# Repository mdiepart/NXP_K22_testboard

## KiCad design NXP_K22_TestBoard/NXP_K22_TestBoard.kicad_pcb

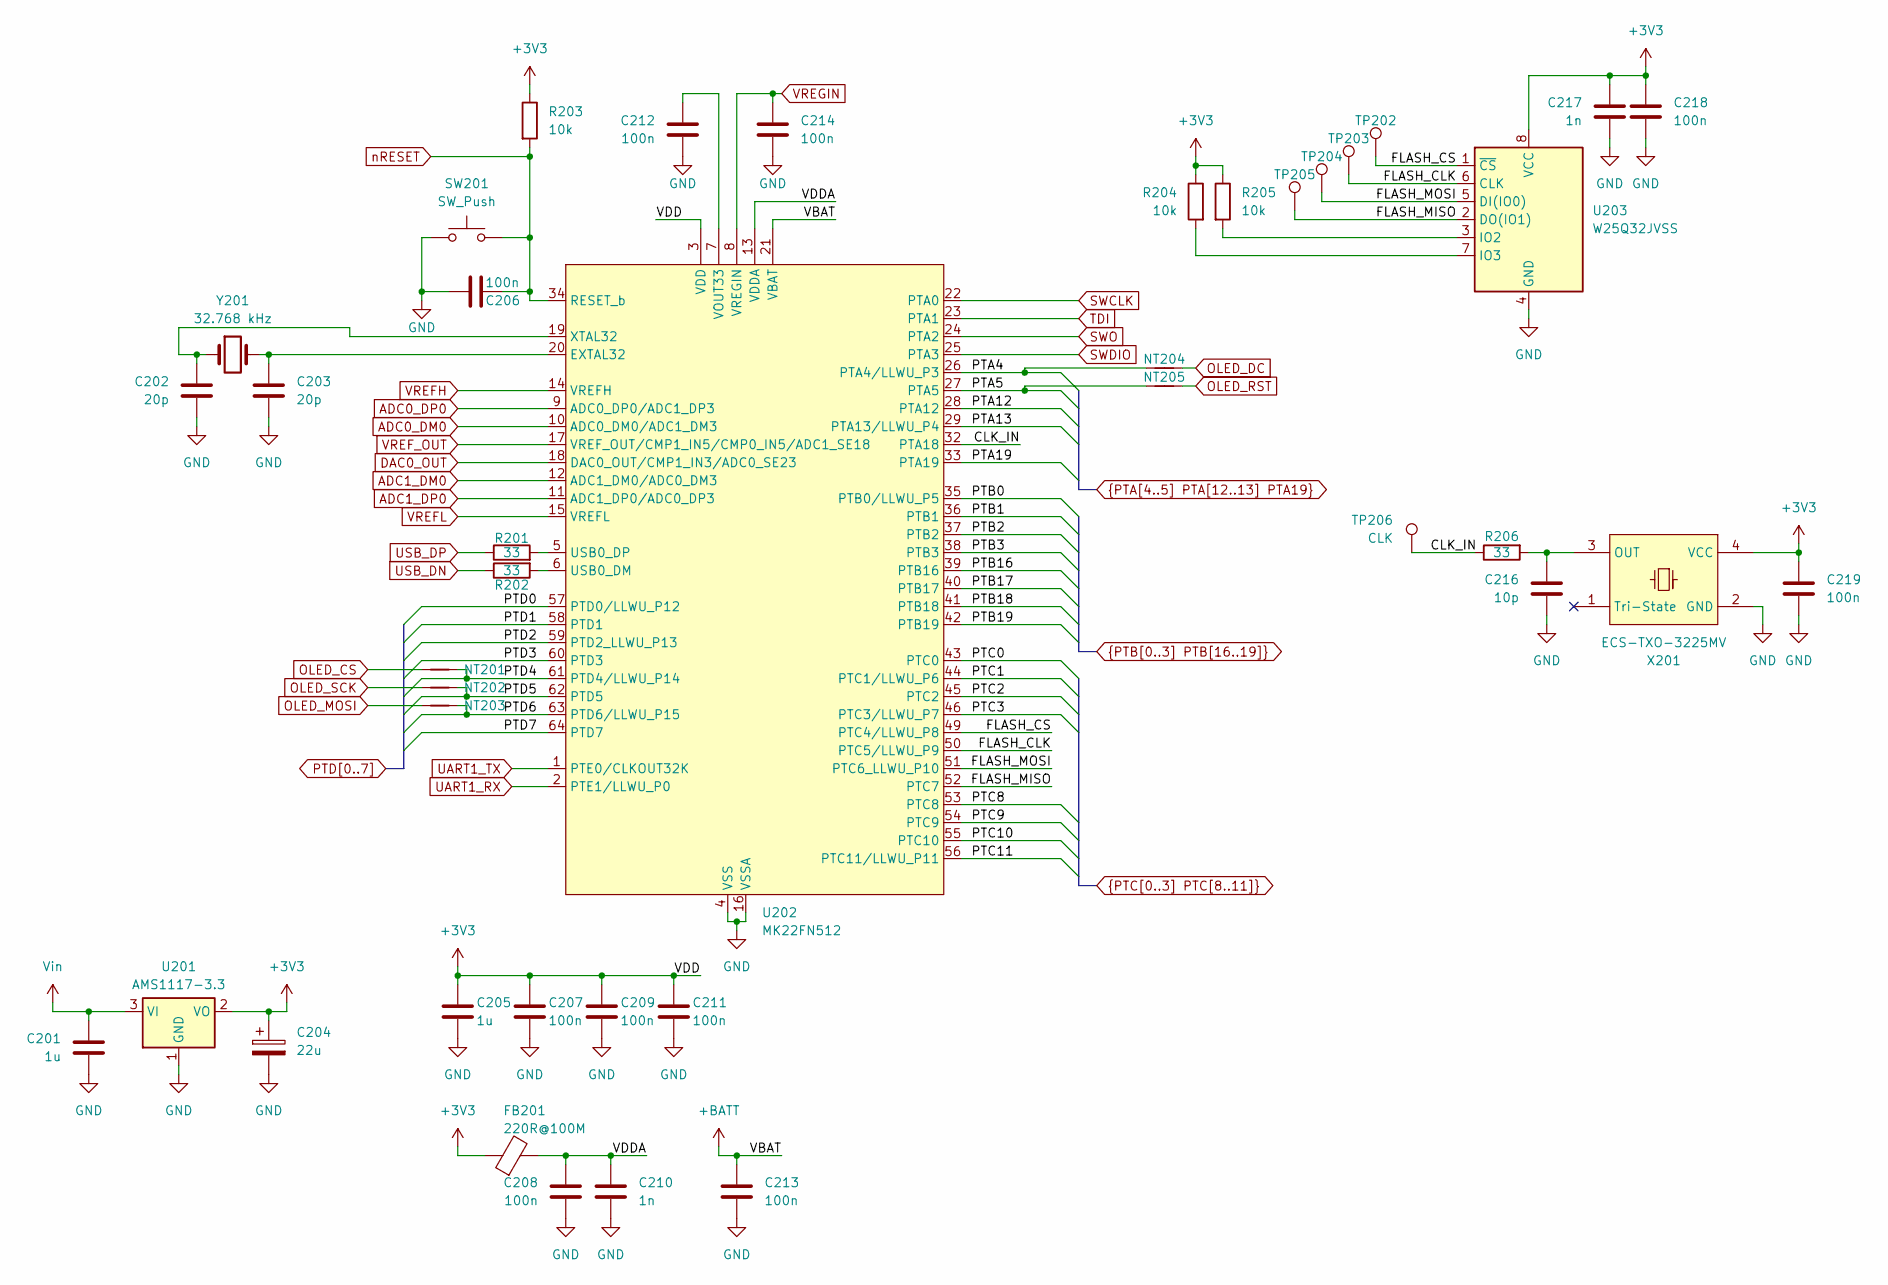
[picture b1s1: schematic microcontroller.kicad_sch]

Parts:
C201, C205: 1u; C_0603_1608Metric; MPN Generic C/1uF/X7R/50V/0603
C202, C203: 20p; C_0603_1608Metric; MPN Generic C/12pF/C0G/50V/0603
C204: 22u; CP_EIA-7343-31_Kemet-D; MPN T495D226K035ATE125; LCSC Part # C122325
C206, C207, C208, C209, C211, C212, C213, C214, C218, C219: 100n; C_0603_1608Metric; MPN Generic C/100nF/X7R/16V/0603
C210, C217: 1n; C_0603_1608Metric; MPN Generic C/1nF/X7R/16V/0603
C216: 10p; C_0603_1608Metric; MPN Generic C/10pF/C0G/50V/0603
FB201: 220R@100M; L_0603_1608Metric; MPN MPZ1608Y221BTA00; LCSC Part # C275489
NT201, NT202, NT203, NT204, NT205: NetTie_2; NetTie-2_SMD_Pad0.2mm
R201, R202, R206: 33; R_0603_1608Metric; MPN Generic R/33R/0603
R203, R204, R205: 10k; R_0603_1608Metric; MPN Generic R/10k/0603
SW201: SW_Push; SW_SPST_PTS645; MPN PTS645SH50SMTR92LFS; LCSC Part # C221869
TP202, TP203, TP204, TP205: TestPoint; TestPoint_Pad_D1.5mm
TP206: CLK; TestPoint_Pad_D2.0mm
U201: AMS1117-3.3; SOT-223-3_TabPin2; MPN AMS1117-3.3; LCSC Part # C6186
U202: MK22FN512; LQFP-64_10x10mm_P0.5mm; MPN MK22FN512VLH12
U203: W25Q32JVSS; SOIC-8_5.23x5.23mm_P1.27mm; MPN W25Q32JVSSIQ; LCSC Part # C179173
X201: ECS-TXO-3225MV; ECS-TXO_3.2x2.5mm; MPN ECS-TXO-3225MV-122.8-TR; LCSC Part # C5355149
Y201: 32.768 kHz; Crystal_SMD_3215-2Pin_3.2x1.5mm; MPN Q13FC1350000400; LCSC Part # C32346

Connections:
+3V3: C204.1, C205.1, C207.1, C209.1, C211.1, C217.1, C218.1, C219.1, FB201.1, R203.1, R204.1, R205.1, U201.2 (VO), U202.3 (VDD), U202.30 (VDD), U202.48 (VDD), U203.8 (VCC), X201.4 (VCC); also elsewhere on the board
+BATT: C213.1, U202.21 (VBAT); also elsewhere on the board
/Microcontroller/CLK_IN: R206.1, TP206.1, U202.32 (PTA18)
/Microcontroller/FLASH_CLK: TP203.1, U202.50 (PTC5/LLWU_P9), U203.6 (CLK)
/Microcontroller/FLASH_CS: TP202.1, U202.49 (PTC4/LLWU_P8), U203.1 (~CS)
/Microcontroller/FLASH_MISO: TP205.1, U202.52 (PTC7), U203.2 (DO(IO1))
/Microcontroller/FLASH_MOSI: TP204.1, U202.51 (PTC6_LLWU_P10), U203.5 (DI(IO0))
/Microcontroller/VDDA: C208.1, C210.1, FB201.2, U202.13 (VDDA)
ADC0_DM0: U202.10 (ADC0_DM0/ADC1_DM3); also elsewhere on the board
ADC0_DP0: U202.9 (ADC0_DP0/ADC1_DP3); also elsewhere on the board
ADC1_DM0: U202.12 (ADC1_DM0/ADC0_DM3); also elsewhere on the board
ADC1_DP0: U202.11 (ADC1_DP0/ADC0_DP3); also elsewhere on the board
DAC0_OUT: U202.18 (DAC0_OUT/CMP1_IN3/ADC0_SE23); also elsewhere on the board
GND: C201.2, C202.2, C203.2, C204.2, C205.2, C206.2, C207.2, C208.2, C209.2, C210.2, C211.2, C212.2, C213.2, C214.2, C216.2, C217.2, C218.2, C219.2, SW201.1, U201.1 (GND), U202.4 (VSS), U202.16 (VSSA), U202.31 (VSS), U202.47 (VSS), U203.4 (GND), X201.2 (GND); also elsewhere on the board
unnamed: C203.1, U202.20 (EXTAL32), Y201.2
unnamed: R202.2, U202.6 (USB0_DM)
unnamed: R201.2, U202.5 (USB0_DP)
unnamed: C212.1, U202.7 (VOUT33)
unnamed: C202.1, U202.19 (XTAL32), Y201.1
unnamed: R205.2, U203.3 (IO2)
unnamed: R204.2, U203.7 (IO3)
unnamed: C216.1, R206.2, X201.3 (OUT)
OLED_CS: NT201.1; also elsewhere on the board
OLED_DC: NT204.2; also elsewhere on the board
OLED_MOSI: NT203.1; also elsewhere on the board
OLED_RST: NT205.2; also elsewhere on the board
OLED_SCK: NT202.1; also elsewhere on the board
PTA4: NT204.1, U202.26 (PTA4/LLWU_P3); also elsewhere on the board
PTA5: NT205.1, U202.27 (PTA5); also elsewhere on the board
PTA12: U202.28 (PTA12); also elsewhere on the board
PTA13: U202.29 (PTA13/LLWU_P4); also elsewhere on the board
PTA19: U202.33 (PTA19); also elsewhere on the board
PTB0: U202.35 (PTB0/LLWU_P5); also elsewhere on the board
PTB1: U202.36 (PTB1); also elsewhere on the board
PTB2: U202.37 (PTB2); also elsewhere on the board
PTB3: U202.38 (PTB3); also elsewhere on the board
PTB16: U202.39 (PTB16); also elsewhere on the board
PTB17: U202.40 (PTB17); also elsewhere on the board
PTB18: U202.41 (PTB18); also elsewhere on the board
PTB19: U202.42 (PTB19); also elsewhere on the board
PTC0: U202.43 (PTC0); also elsewhere on the board
PTC1: U202.44 (PTC1/LLWU_P6); also elsewhere on the board
PTC2: U202.45 (PTC2); also elsewhere on the board
PTC3: U202.46 (PTC3/LLWU_P7); also elsewhere on the board
PTC8: U202.53 (PTC8); also elsewhere on the board
PTC9: U202.54 (PTC9); also elsewhere on the board
PTC10: U202.55 (PTC10); also elsewhere on the board
PTC11: U202.56 (PTC11/LLWU_P11); also elsewhere on the board
PTD0: U202.57 (PTD0/LLWU_P12); also elsewhere on the board
PTD1: U202.58 (PTD1); also elsewhere on the board
PTD2: U202.59 (PTD2_LLWU_P13); also elsewhere on the board
PTD3: U202.60 (PTD3); also elsewhere on the board
PTD4: NT201.2, U202.61 (PTD4/LLWU_P14); also elsewhere on the board
PTD5: NT202.2, U202.62 (PTD5); also elsewhere on the board
PTD6: NT203.2, U202.63 (PTD6/LLWU_P15); also elsewhere on the board
PTD7: U202.64 (PTD7); also elsewhere on the board
SWCLK: U202.22 (PTA0); also elsewhere on the board
SWDIO: U202.25 (PTA3); also elsewhere on the board
SWO: U202.24 (PTA2); also elsewhere on the board
TDI: U202.23 (PTA1); also elsewhere on the board
UART1_RX: U202.2 (PTE1/LLWU_P0); also elsewhere on the board
UART1_TX: U202.1 (PTE0/CLKOUT32K); also elsewhere on the board
USB_DN: R202.1; also elsewhere on the board
USB_DP: R201.1; also elsewhere on the board
VREFH: U202.14 (VREFH); also elsewhere on the board
VREFL: U202.15 (VREFL); also elsewhere on the board
VREF_OUT: U202.17 (VREF_OUT/CMP1_IN5/CMP0_IN5/ADC1_SE18); also elsewhere on the board
VREGIN: C214.1, U202.8 (VREGIN); also elsewhere on the board
Vin: C201.1, U201.3 (VI); also elsewhere on the board
nRESET: C206.1, R203.2, SW201.2, U202.34 (RESET_b); also elsewhere on the board

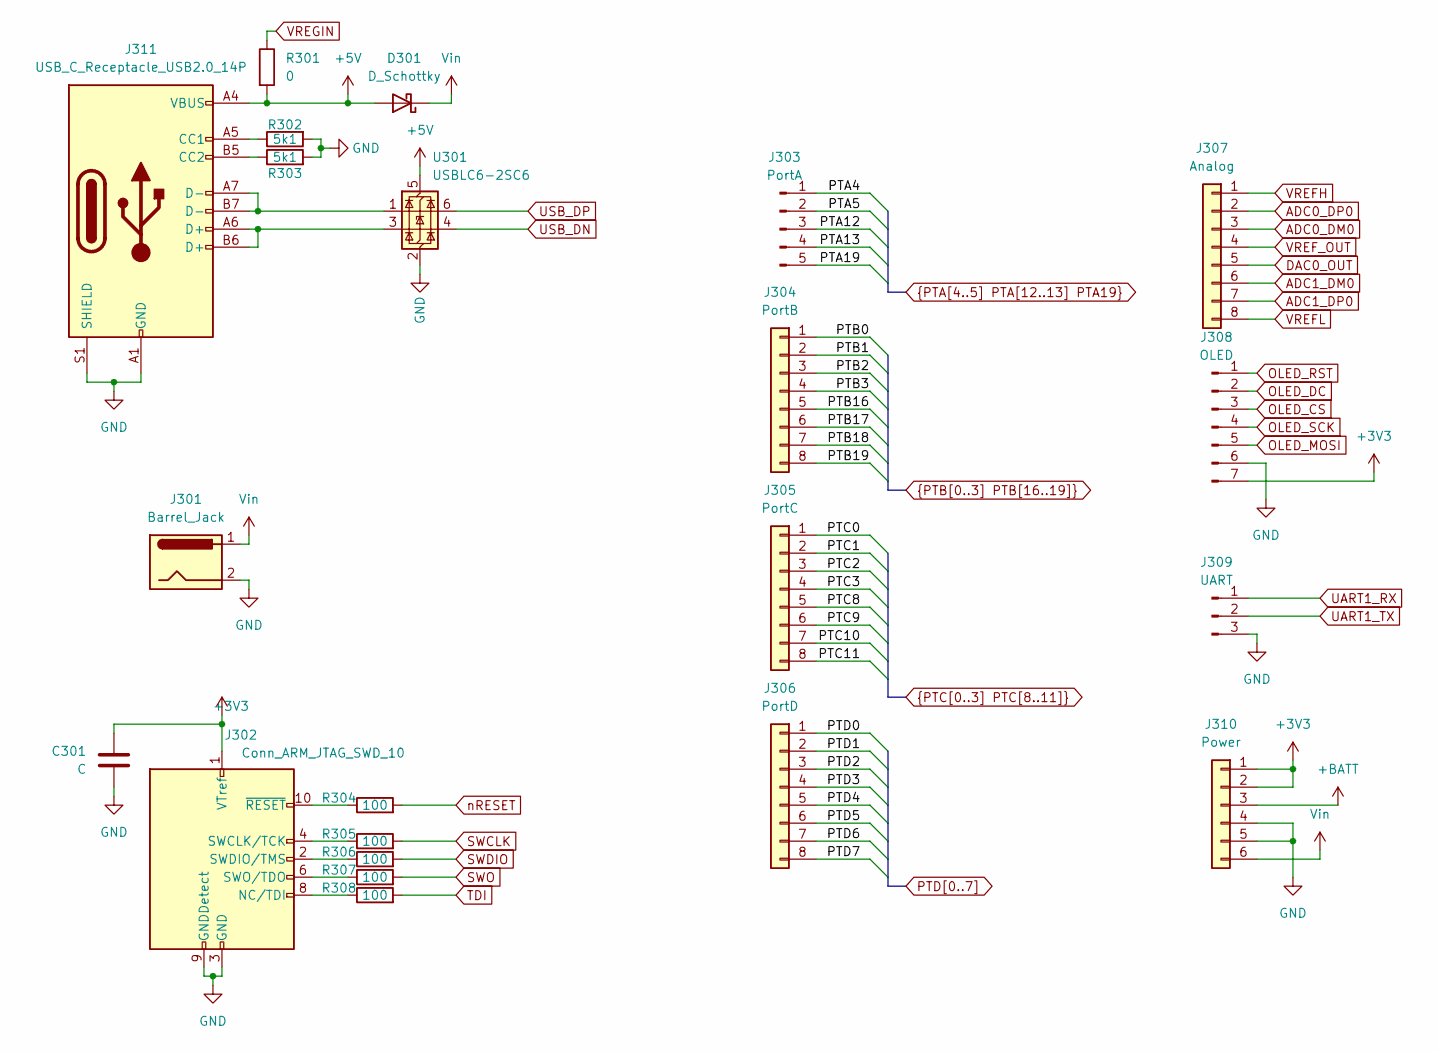
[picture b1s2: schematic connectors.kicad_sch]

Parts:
C301: C; C_0603_1608Metric
D301: D_Schottky; D_SOD-323
J301: Barrel_Jack; BarrelJack_CLIFF_FC681465S_SMT_Horizontal
J302: Conn_ARM_JTAG_SWD_10; PinHeader_2x05_P1.27mm_Vertical_SMD
J303: PortA; PinSocket_1x05_P2.54mm_Vertical
J304: PortB; PinSocket_1x08_P2.54mm_Vertical
J305: PortC; PinSocket_1x08_P2.54mm_Vertical
J306: PortD; PinSocket_1x08_P2.54mm_Vertical
J307: Analog; PinSocket_1x08_P2.54mm_Vertical
J308: OLED; PinSocket_1x07_P2.54mm_Vertical
J309: UART; PinSocket_1x03_P2.54mm_Vertical
J310: Power; PinSocket_1x06_P2.54mm_Vertical
J311: USB_C_Receptacle_USB2.0_14P; USB_C_Receptacle_HRO_TYPE-C-31-M-12
R301: 0; R_0603_1608Metric
R302, R303: 5k1; R_0603_1608Metric
R304, R305, R306, R307, R308: 100; R_0603_1608Metric
U301: USBLC6-2SC6; SOT-23-6

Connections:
+3V3: C301.1, J302.1 (VTref), J308.7, J310.1, J310.2; also elsewhere on the board
+5V: D301.2 (A), J311.A4 (VBUS), J311.A9 (VBUS), J311.B4 (VBUS), J311.B9 (VBUS), R301.2, U301.5 (VBUS)
+BATT: J310.3; also elsewhere on the board
ADC0_DM0: J307.3; also elsewhere on the board
ADC0_DP0: J307.2; also elsewhere on the board
ADC1_DM0: J307.6; also elsewhere on the board
ADC1_DP0: J307.7; also elsewhere on the board
DAC0_OUT: J307.5; also elsewhere on the board
GND: C301.2, J301.2, J302.3 (GND), J302.5 (GND), J302.9 (GNDDetect), J308.6, J309.3, J310.4, J310.5, J311.A1 (GND), J311.A12 (GND), J311.B1 (GND), J311.B12 (GND), J311.S1 (SHIELD), R302.2, R303.2, U301.2 (GND); also elsewhere on the board
unnamed: J302.8 (NC/TDI), R308.1
unnamed: J302.4 (SWCLK/TCK), R305.1
unnamed: J302.2 (SWDIO/TMS), R306.1
unnamed: J302.6 (SWO/TDO), R307.1
unnamed: J302.10 (~RESET), R304.1
unnamed: J311.A5 (CC1), R302.1
unnamed: J311.B5 (CC2), R303.1
unnamed: J311.A6 (D+), J311.B6 (D+), U301.3 (I/O2)
unnamed: J311.A7 (D-), J311.B7 (D-), U301.1 (I/O1)
OLED_CS: J308.3; also elsewhere on the board
OLED_DC: J308.2; also elsewhere on the board
OLED_MOSI: J308.5; also elsewhere on the board
OLED_RST: J308.1; also elsewhere on the board
OLED_SCK: J308.4; also elsewhere on the board
PTA4: J303.1; also elsewhere on the board
PTA5: J303.2; also elsewhere on the board
PTA12: J303.3; also elsewhere on the board
PTA13: J303.4; also elsewhere on the board
PTA19: J303.5; also elsewhere on the board
PTB0: J304.1; also elsewhere on the board
PTB1: J304.2; also elsewhere on the board
PTB2: J304.3; also elsewhere on the board
PTB3: J304.4; also elsewhere on the board
PTB16: J304.5; also elsewhere on the board
PTB17: J304.6; also elsewhere on the board
PTB18: J304.7; also elsewhere on the board
PTB19: J304.8; also elsewhere on the board
PTC0: J305.1; also elsewhere on the board
PTC1: J305.2; also elsewhere on the board
PTC2: J305.3; also elsewhere on the board
PTC3: J305.4; also elsewhere on the board
PTC8: J305.5; also elsewhere on the board
PTC9: J305.6; also elsewhere on the board
PTC10: J305.7; also elsewhere on the board
PTC11: J305.8; also elsewhere on the board
PTD0: J306.1; also elsewhere on the board
PTD1: J306.2; also elsewhere on the board
PTD2: J306.3; also elsewhere on the board
PTD3: J306.4; also elsewhere on the board
PTD4: J306.5; also elsewhere on the board
PTD5: J306.6; also elsewhere on the board
PTD6: J306.7; also elsewhere on the board
PTD7: J306.8; also elsewhere on the board
SWCLK: R305.2; also elsewhere on the board
SWDIO: R306.2; also elsewhere on the board
SWO: R307.2; also elsewhere on the board
TDI: R308.2; also elsewhere on the board
UART1_RX: J309.1; also elsewhere on the board
UART1_TX: J309.2; also elsewhere on the board
USB_DN: U301.4 (I/O2); also elsewhere on the board
USB_DP: U301.6 (I/O1); also elsewhere on the board
VREFH: J307.1; also elsewhere on the board
VREFL: J307.8; also elsewhere on the board
VREF_OUT: J307.4; also elsewhere on the board
VREGIN: R301.1; also elsewhere on the board
Vin: D301.1 (K), J301.1, J310.6; also elsewhere on the board
nRESET: R304.2; also elsewhere on the board

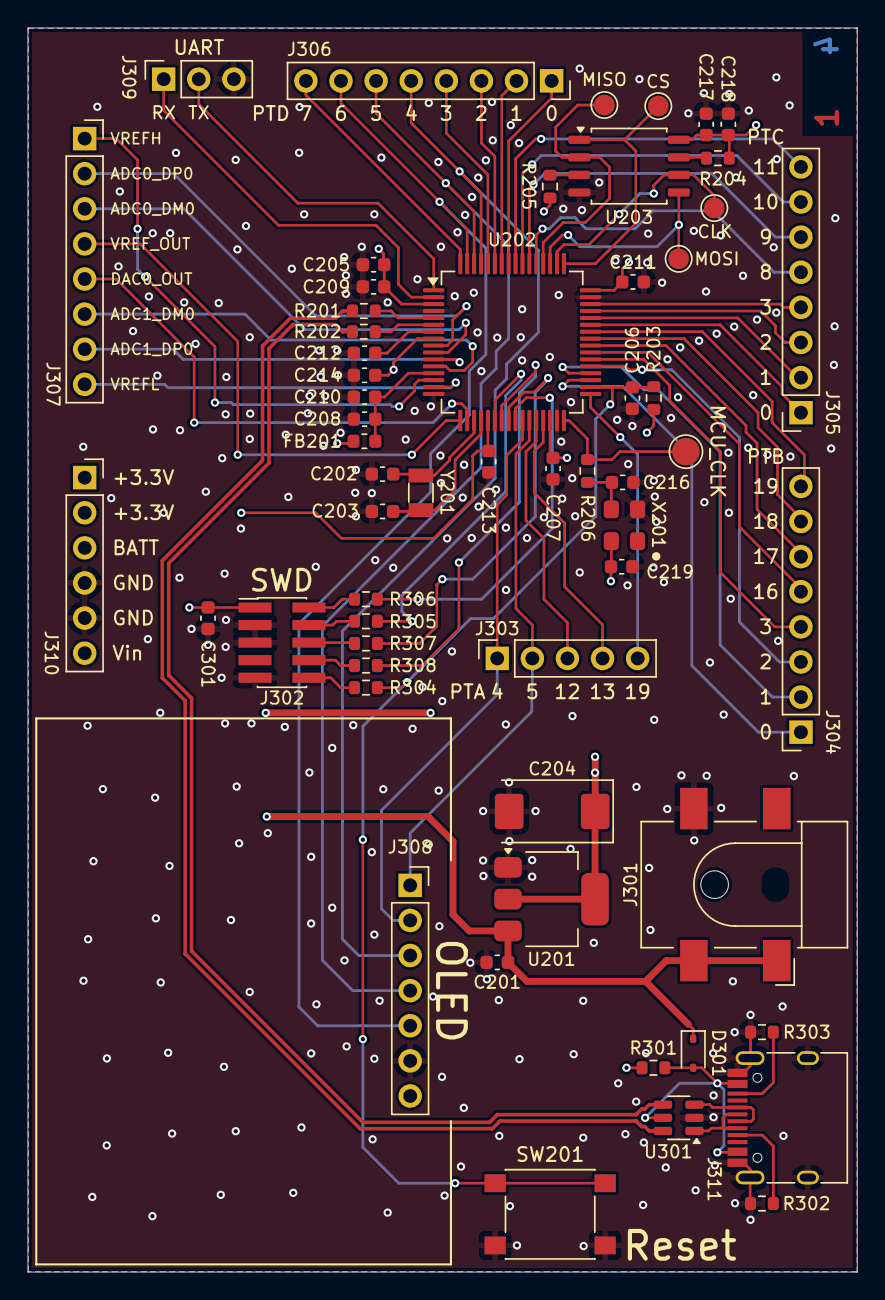
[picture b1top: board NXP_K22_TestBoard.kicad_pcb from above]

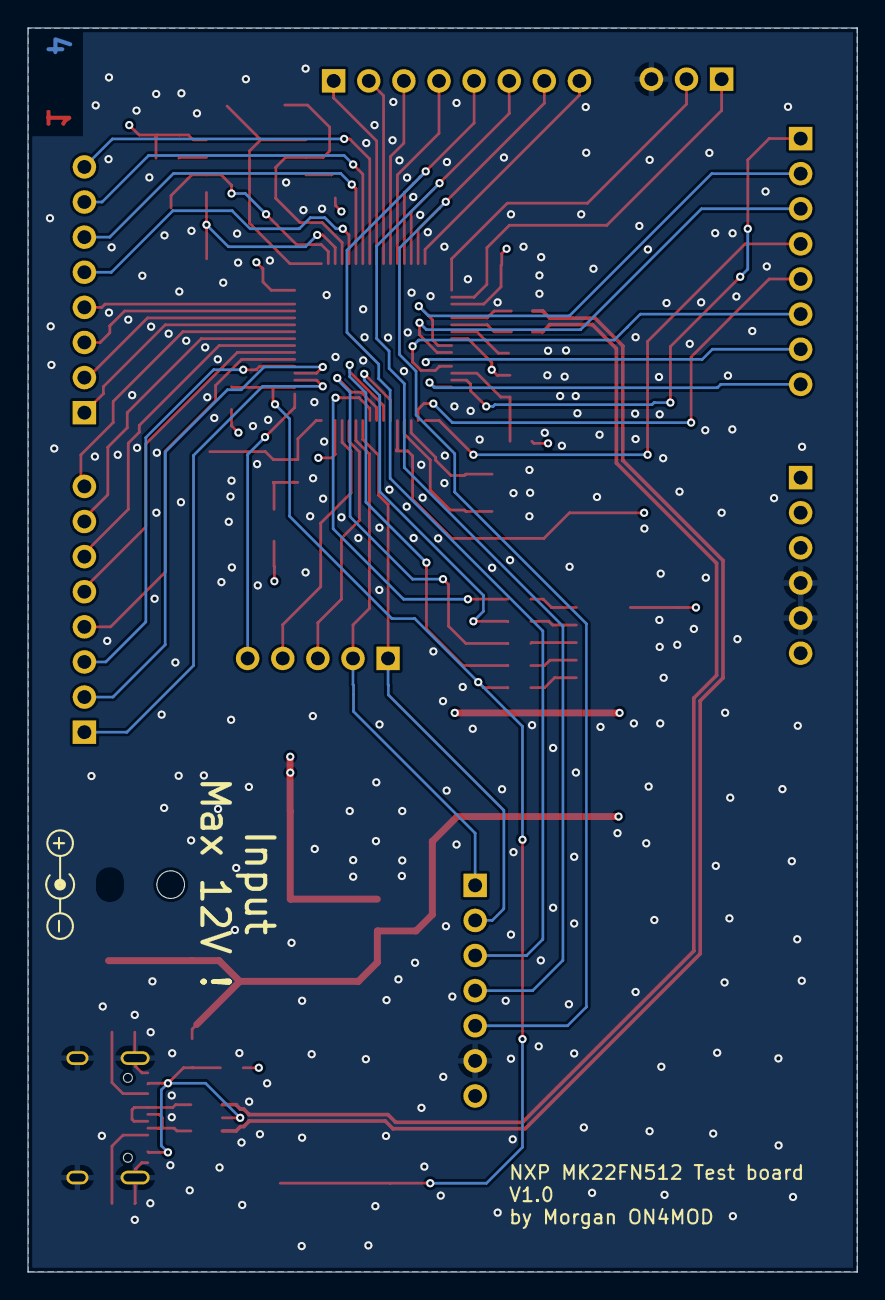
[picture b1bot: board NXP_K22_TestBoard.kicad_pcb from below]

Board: 4 copper layers, 60.0 x 90.0 mm, 63 parts (5 on the bottom side), 80 nets.

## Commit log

2024-02-20 Init Kicad Project
2024-03-09 [WIP] Added board
2024-03-10 Switched M17_kicad_library branch to KiCad 8
2024-03-10 Finished board layout
    Design rules not checked yet
2024-03-12 Finishing touches
    Set manufacturing constraints to JLCPCB constraints, set USB differential pair to correct width/spacing.
    Set-up pcb characteristics, added descriptions to user comments layer, fixed power regulator footprint being outdated.
